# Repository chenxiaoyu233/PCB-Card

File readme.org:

I always want to build some customized devices for myself, in which I have to implement both the hardware and the software.
I am quite familiar with softare development but only with little experience for the hardware development.

To implement the hardware, the most important part seems to be the design of printed circuit board (PCB).
And this project aims at gaining such kind of experience.

* The Card-V1 Project
** Startup
    First, I install the KiCad on my mac and I learn how to use it on bilibili.
    At the beginning, I randomly choose a MCU on [[https://list.szlcsc.com/][立创商城]], which is named as STM32L073RBT6 (about ¥50).
    Then I try to design the PCB according to this chip.

** Design the Schematic
    The most frustrated part in this step is to answer the question about how to driven the STM32L073RBT6 chip.
    That is, I want to know the "smallest" working requirement of this chip.
    Besides, I also need to figure out how to achieve these requirements on the PCB.
    Luckly, after a very long time, I find an article about how to achieve this ([[./doc/an4467-getting-started-with-stm32l0xx-hardware-development-stmicroelectronics.pdf][STM32L0xx-Hardware]]).

    Another question is to write my program into the chip.
    I find out that STM32L073RBT6 support USB DFU protocol in [[./doc/STM32-BOOT.pdf][STM32-BOOT]] (section 37.1).
    And I plan to download my program by a USB type-C port.
    Now, the question is, how to connect the USB prot to STM32L073RBT6 ?
    I find the answer in [[./doc/STM32-USB-Hardware.pdf][STM32-USB-Hardware]] (section 3.1.2).
    The USB port also handles the power supply.

    For future concern, I also add a circuit for a 1.54 inch e-paper screen ([[https://www.waveshare.net/shop/1.54inch-e-Paper-B.htm][e-paper-screen]]).
    The final result is like
    [[./readme-mat/原理图.png]]

** Design the PCB layout
    This step is quite simple because my pcb only runs at low speed.
    The final result is
    [[./readme-mat/pcb.png]]

** Order and Assemble
    I bought all the materials on [[https://list.szlcsc.com/][立创商城]] (about ¥60/suit) and order the PCB on [[https://www.jlc.com][嘉立创]] (about ¥30 for 5 PCBs).
    I assemble and weld these materials by using a heat gun.
    Here is the results.
    [[./readme-mat/IMG_1441.jpg]]
    [[./readme-mat/IMG_1442.jpg]]
    [[./readme-mat/IMG_1443.jpg]]

** Write Software and Blink the LED
    The document provided by ST ([[./doc/STM32L0x3-man.pdf][STM32L0x3-Manual]]) is very frustrated to read.
    It is so long and makes you confused about where to start.
    The crucial information for us is the boot mechanism of the chip.

    The chip has a RAM at =0x20002000= - =0x20004FFF= and a read-only flash memory at =0x08000000= - =0x0802FFFF=.
    When BOOT0 pin is set to 1, the chip runs a hard coded bootloader specified in [[./doc/STM32-BOOT.pdf][STM32-BOOT]] (section 37.1).
    This bootloader supports USB DFU protocol, which allows us to download our executables to the chip by the tool =dfu-util=.
    Our program need to be written in the beginning of the flash memory at =0x08000000=.

    When BOOT0 pin is set to 0, the chip initialized as follows:
    1. set the 32bit at =0x08000000= - =0x08000003= to register =SP=, which always point to the top of the stack (the stack grow towards 0).
       Typically, these 32bit should be set as =0x20004FFF= as the bottom of the RAM.
    2. set the 32bit at =0x08000004= - =0x08000007= to register =PC=, which is the program counter.

    This indicates us about how to initialize in our program.

    Now, since we connect the LEDs to the GPIOB ports of the chip, we only need to write 1 to GPIOB port to enlighten the LEDs.
    To do this, we need first enable the GPIOB ports at =RCC_IOPENR= register ([[./doc/STM32L0x3-man.pdf][STM32L0x3-Manual]], section 7.3.12).
    (I miss this step at first, and it tooks me a lot of time to figure out what happens).
    Then, we need to initialize the GPIOB ports by =GPIOB_MODER=, =GPIOB_OTYPER=, =GPIOB_OSPEEDR=, =GPIOB_PUPDR=, =GPIOB_ODR= registers ([[./doc/STM32L0x3-man.pdf][STM32L0x3-Manual]], section 9.4).
    These registers could be accessed using certain memory address.

    All the code could find at [[./code][code]].

** Debug
    Since I only use USB port to download the program, my PCB lacks debug infrastructure like SWD and ST-Link.
    So, I cannot do any on-board debugging, which makes it really hard to find out whats going wrong.

    Luckily, I could use qemu to simulate the STM32 and run my program on it first.
    Though the model is not exactly the same, it still helps me a lot.
    The material on [[./doc/STM32L0x3-man.pdf][STM32L0x3-Manual]] for the boot behavior is very ambiguous, you have to do some experiment to figure out what happens.

** Final Results
    [[./readme-mat/output.gif]]
    
* The Card-V2 Project
  Based on the same hardware, the "card" could be use to drive an e-paper dispaly:  [[https://www.waveshare.net/shop/1.54inch-e-Paper.htm][wareshare 1.54inch e-paper]].
  During the development, I find that I use the wrong type of FPC connector, the original one is replaced by [[https://item.szlcsc.com/3194063.html][0425-A-A04-002 (C2911807)]].
  Moreover, the welding is really difficult and it tooks me tons of time to debug.

** Final Results
    Most code is generated by a tool called =STM32CubeMX=.
    The code is placed in [[./USBLib]] and could be build using =make=.
    Before using =make=, one should find an image of 200x200 and run =image-bin.py= in the folder =EPD= to convert it into a c header.

    The result is like:
    [[./readme-mat/IMG_1450.jpg]]

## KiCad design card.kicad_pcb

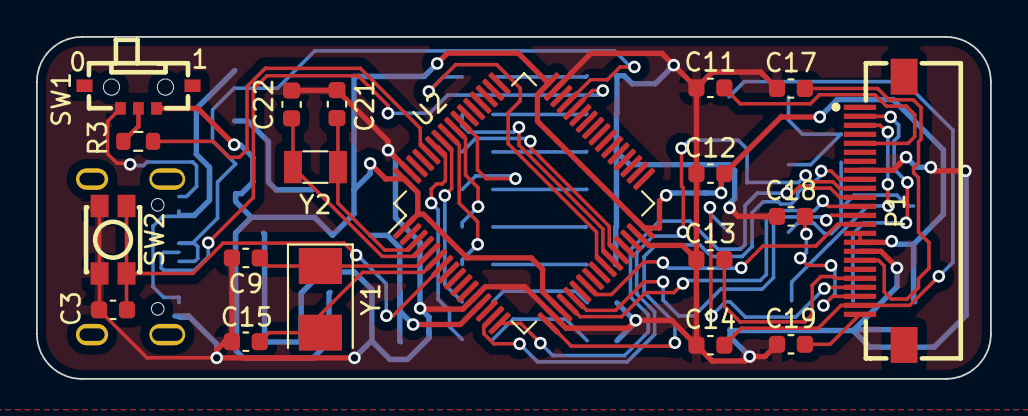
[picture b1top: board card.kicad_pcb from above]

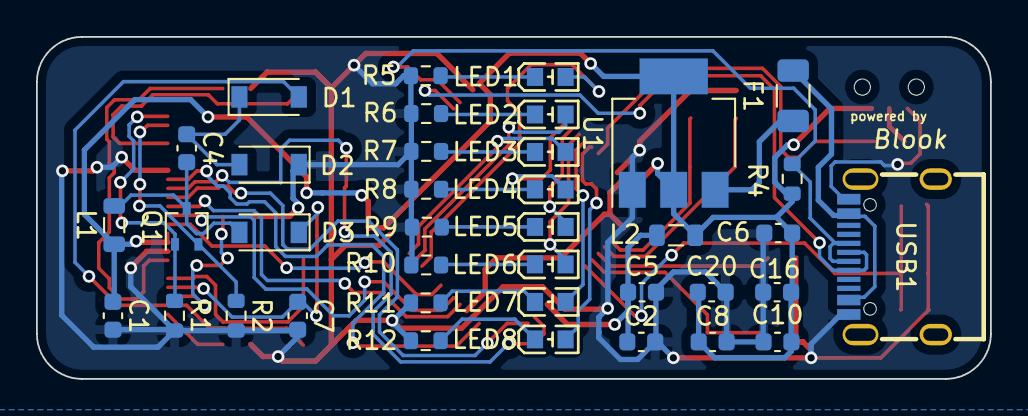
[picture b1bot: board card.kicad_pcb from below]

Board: 2 copper layers, 53.0 x 19.0 mm, 57 parts (38 on the bottom side), 47 nets.

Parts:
C1, C4: 4.7uF/50V; C_0603_1608Metric
C2, C3, C6, C8, C10, C16: 100nF; C_0603_1608Metric
C5, C20: 1uF; C_0603_1608Metric
C7, C11, C12, C13, C14, C17, C18, C19: 1uF/50V; C_0603_1608Metric
C9, C15, C21, C22: 10pF; C_0603_1608Metric
D1, D2, D3: MBR0530; D_SOD-123
F1: Fuse_500mA; Fuse_1206_3216Metric
L1, L2: 10uH; L_0805_2012Metric
LED1, LED2, LED3, LED4, LED5, LED6, LED7, LED8: GT-197; LED0603-FD
P1: KH-FG0.5-H2.0-24PIN; FPC-SMD_KH-FG0.5-H2.0-24PIN
Q1: Si1308EDL; SOT-323_SC-70
R1, R3: 10K; R_0603_1608Metric
R2: 3; R_0603_1608Metric
R4: 1.5K; R_0603_1608Metric
R5, R6, R7, R8, R9, R10, R11, R12: 1K; R_0603_1608Metric
SW1: MK-11C04-G013; SW-SMD_MK-11C04-G013
SW2: ST-1185S-4P; SW-SMD_ST-1185S-4P
U1: AMS1117-3.3; SOT-223-3_TabPin2
U2: STM32L072RBT6; LQFP-64_10x10mm_P0.5mm
USB1: KH-TYPE-C-16P-T; USB-C-SMD_KH-TYPE-C-16P
Y1: 8MHz; Crystal_SMD_5032-2Pin_5.0x3.2mm
Y2: 32.768KHz; Crystal_SMD_3215-2Pin_3.2x1.5mm

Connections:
+5V: F1.1, USB1.A4 (VBUS), USB1.A9 (VBUS), USB1.B4 (VBUS), USB1.B9 (VBUS)
/GDR: P1.2 (GDR), Q1.1, R1.1
/PB0: LED1.1 (A), U2.26 (PB0)
/PB1: LED2.1 (A), U2.27 (PB1)
/PB2: LED3.1 (A), U2.28 (PB2)
/PB3: LED4.1 (A), U2.55 (PB3)
/PB4: LED5.1 (A), U2.56 (PB4)
/PB5: LED6.1 (A), U2.57 (PB5)
/PB6: LED7.1 (A), U2.58 (PB6)
/PB7: LED8.1 (A), U2.59 (PB7)
/PREVGH: C7.1, D3.1 (K), P1.21 (PREVGH)
/PREVGL: C14.2, D1.2 (A), P1.23 (PREVGL)
/RESE: P1.3 (RESE), Q1.2, R2.1
BOOT0: R3.2, U2.60 (BOOT0)
BUSY: P1.9 (BUSY), U2.17 (PA3)
CLK: P1.13 (SCL), U2.21 (PA5)
CS: P1.12 (CS), U2.20 (PA4)
DIN: P1.14 (SDA), U2.23 (PA7)
DM: U2.44 (PA11), USB1.A7 (D-), USB1.B7 (D-)
DP: R4.2, U2.45 (PA12), USB1.A6 (D+), USB1.B6 (D+)
D/C: P1.11 (D/C), U2.16 (PA2)
NRST: C3.1, SW2.3, SW2.4, U2.7 (NRST)
unnamed: C4.1, D1.1 (K), D2.2 (A)
unnamed: C4.2, D3.2 (A), L1.2, Q1.3
unnamed: C11.2, P1.5 (VSH2)
unnamed: C13.2, P1.20 (VSH1)
unnamed: C17.2, P1.18 (VDD)
unnamed: C18.2, P1.22 (VSL)
unnamed: C19.2, P1.24 (VCOM)
unnamed: F1.2, U1.3 (VI)
unnamed: LED1.2 (K), R5.1
unnamed: LED2.2 (K), R6.1
unnamed: LED3.2 (K), R7.1
unnamed: LED4.2 (K), R8.1
unnamed: LED5.2 (K), R9.1
unnamed: LED6.2 (K), R10.1
unnamed: LED7.2 (K), R11.1
unnamed: LED8.2 (K), R12.1
unnamed: R3.1, SW1.C
OSC32_IN: C21.1, U2.3 (PC14), Y2.1
OSC32_OUT: C22.1, U2.4 (PC15), Y2.2
OSC_IN: C9.1, U2.5 (PH0), Y1.1
OSC_OUT: C15.1, U2.6 (PH1), Y1.2
RST: P1.10 (RES), U2.15 (PA1)
VDD: C1.1, C6.1, C8.1, C10.1, C12.2, C16.1, C20.1, L1.1, L2.1, P1.15 (VDDIO), P1.16 (VCI), R4.1, SW1.1, U1.2 (VO), U2.1 (VDD), U2.19 (VDD), U2.32 (VDD), U2.48 (VDD_USB), U2.64 (VDD)
VDDA: C2.1, C5.1, L2.2, U2.13 (VDDA)
VSS: C1.2, C2.2, C3.2, C5.2, C6.2, C7.2, C8.2, C9.2, C10.2, C11.1, C12.1, C13.1, C14.1, C15.2, C16.2, C17.1, C18.1, C19.1, C20.2, C21.2, C22.2, D2.1 (K), P1.8 (BS), P1.17 (VSS), R1.2, R2.2, R5.2, R6.2, R7.2, R8.2, R9.2, R10.2, R11.2, R12.2, SW1.2, SW2.1, SW2.2, U1.1 (GND), U2.12 (VSSA), U2.18 (VSS), U2.31 (VSS), U2.47 (VSS), U2.63 (VSS), USB1.A1 (GND), USB1.A12 (GND), USB1.B1 (GND), USB1.B12 (GND)

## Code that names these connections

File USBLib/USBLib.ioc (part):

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Mcu.Name=STM32L073R(B-Z)Tx
Mcu.Package=LQFP64
Mcu.UserName=STM32L073RBTx
PA1.GPIOParameters=GPIO_Speed
PA1.GPIO_Speed=GPIO_SPEED_FREQ_VERY_HIGH
PA1.Signal=GPIO_Output
PA2.GPIOParameters=GPIO_Speed
PA2.GPIO_Speed=GPIO_SPEED_FREQ_VERY_HIGH
PA2.Signal=GPIO_Output
PA3.Signal=GPIO_Input
PA4.GPIOParameters=GPIO_Speed
PA4.GPIO_Speed=GPIO_SPEED_FREQ_VERY_HIGH
PA4.Signal=GPIO_Output
PA5.GPIOParameters=GPIO_Speed
PA5.GPIO_Speed=GPIO_SPEED_FREQ_VERY_HIGH
PA5.Signal=GPIO_Output
PA7.GPIOParameters=GPIO_Speed
PA7.GPIO_Speed=GPIO_SPEED_FREQ_VERY_HIGH
PA7.Signal=GPIO_Output
PB0.Signal=GPIO_Output
PB1.Signal=GPIO_Output
PB2.Signal=GPIO_Output
PB3.Signal=GPIO_Output
PB4.Signal=GPIO_Output
PB5.Signal=GPIO_Output
PB6.Signal=GPIO_Output
PB7.Signal=GPIO_Output
RCC.HSE_VALUE=8000000
RCC.SYSCLKFreq_VALUE=16000000
RCC.SYSCLKSource=RCC_SYSCLKSOURCE_HSI
board=custom

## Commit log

2022-08-18 Release Card-V1
    driven on-chip led
2022-08-18 minor
2022-08-18 [readme]
2022-08-31 Card-V2
    add e-paper display support
